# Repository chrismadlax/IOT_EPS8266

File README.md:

# IOT_EPS8266
IOT_EPS8266

for Maker's Attic 創客閣樓

_PCB: Eagle PCB project 

_CODE: uPy source code 

problem fix
	transistor T1 & T2 pin E/B must swap
	crystal can be remove
	resistance R19 can be short to GND

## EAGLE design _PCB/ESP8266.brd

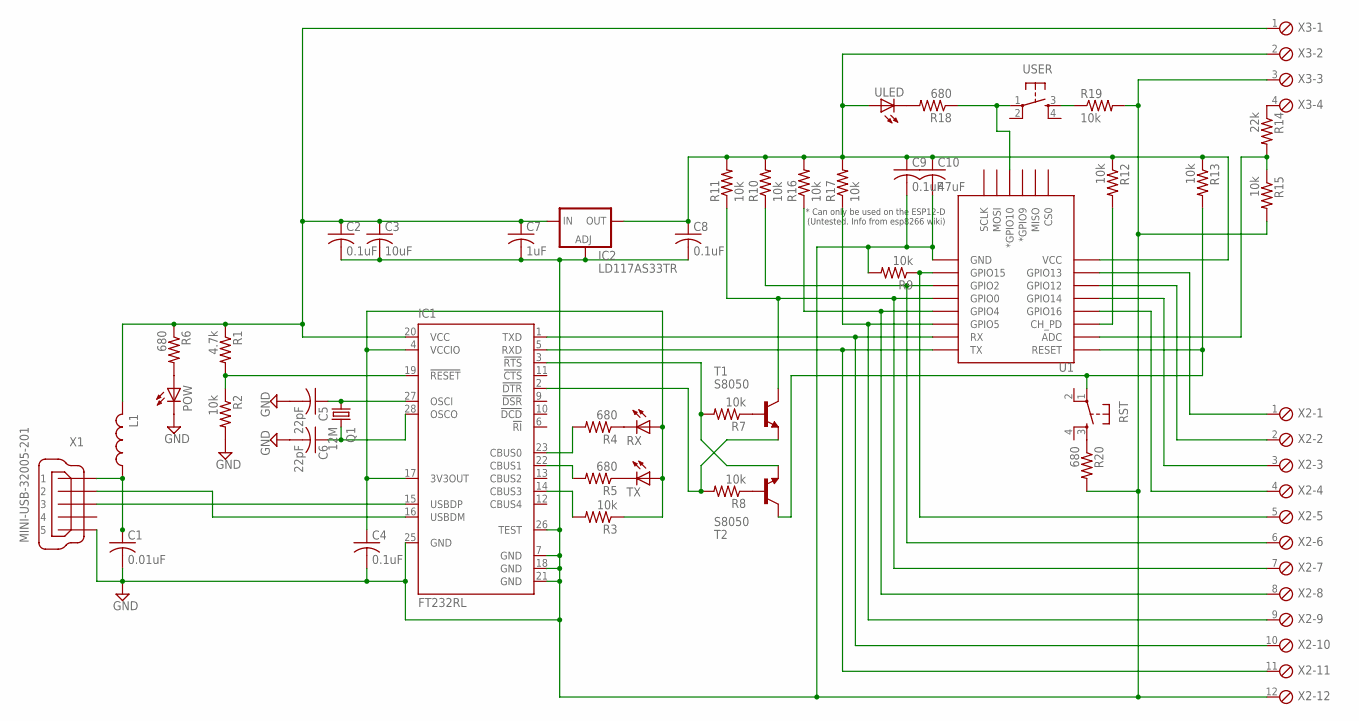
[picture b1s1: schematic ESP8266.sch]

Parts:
C1: 0.01uF; C0805
C2, C4, C8, C9: 0.1uF; C0805
C3: 10uF; C0805
C5, C6: 22pF; C0805
C7: 1uF; C0805
C10: 47uF; C0805
IC1: FT232RL; SSOP28
IC2: LD117AS33TR; SOT223
L1: L-USL2012C; L2012C
POW: LEDCHIP-LED0805; CHIP-LED0805
Q1: 12M; SM49
R1: 4.7k; R0805
R2, R3, R7, R8, R9, R10, R11, R12, R13, R15, R16, R17, R19: 10k; R0805
R4, R5, R6, R18, R20: 680; R0805
R14: 22k; R0805
RST: DTSM-6
RX: LEDCHIP-LED0805; CHIP-LED0805
T1, T2: S8050; SOT23-BEC
TX: LEDCHIP-LED0805; CHIP-LED0805
U1: ESP12ESMD; ESP12E-SMD
ULED: LEDCHIP-LED0805; CHIP-LED0805
USER: DTSM-6
X1: MINI-USB-32005-201; 32005-201
X2: MPT12; 12POL254
X3: MPT4; 4POL254

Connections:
GND: C1.2, C2.2, C3.2, C4.2, C5.2, C6.2, C7.2, C8.2, C9.2, C10.2, IC1.7 (GND), IC1.18 (GND), IC1.21 (GND), IC1.25 (GND), IC1.26 (TEST), IC2.1 (ADJ), POW.C, R2.2, R9.2, R15.2, R19.2, R20.2, U1.GND, X1.5, X2.12, X3.3
unnamed: POW.A, R6.2
unnamed: IC1.15 (USBDP), X1.3
unnamed: IC1.16 (USBDM), X1.2
unnamed: C5.1, IC1.27 (OSCI), Q1.1
unnamed: C6.1, IC1.28 (OSCO), Q1.2
unnamed: IC1.19 (!RESET), R1.2, R2.1
unnamed: IC1.14 (CBUS3), R3.2
unnamed: IC1.22 (CBUS1), R5.2
unnamed: IC1.23 (CBUS0), R4.2
unnamed: R4.1, RX.C
unnamed: R5.1, TX.C
unnamed: IC1.1 (TXD), U1.RXD0 (RX), X2.10
unnamed: IC1.5 (RXD), U1.TXD0 (TX), X2.11
unnamed: R7.1, T1.B
unnamed: R8.1, T2.B
unnamed: IC1.3 (!RTS), R7.2, T2.E
unnamed: IC1.2 (!DTR), R8.2, T1.E
unnamed: R10.1, U1.GPIO2, X2.6
unnamed: R9.1, U1.GPIO15, X2.5
unnamed: R16.1, U1.GPIO4, X2.8
unnamed: R12.2, U1.CH_PD
unnamed: R13.2, RST.1, T2.C, U1.RESET
unnamed: C4.1, IC1.4 (VCCIO), IC1.17 (3V3OUT), R3.1, RX.A, TX.A
unnamed: R14.2, R15.1, U1.ADC
unnamed: R17.1, U1.GPIO5, X2.9
unnamed: R11.1, T1.C, U1.GPIO0, X2.7
unnamed: R18.2, ULED.C
unnamed: R18.1, U1.GPIO10 (*GPIO10), USER.1
unnamed: R19.1, USER.3
unnamed: R14.1, X3.4
unnamed: R20.1, RST.3
unnamed: U1.GPIO13, X2.1
unnamed: U1.GPIO12, X2.2
unnamed: U1.GPIO14, X2.3
unnamed: U1.GPIO16, X2.4
V33E: C8.1, C9.1, C10.1, IC2.4 (OUT), R10.2, R11.2, R12.1, R13.1, R16.2, R17.2, U1.VCC, ULED.A, X3.2
VBUS: C1.1, L1.1, X1.1
VCC: C2.1, C3.1, C7.1, IC1.20 (VCC), IC2.3 (IN), L1.2, R1.1, R6.1, X3.1

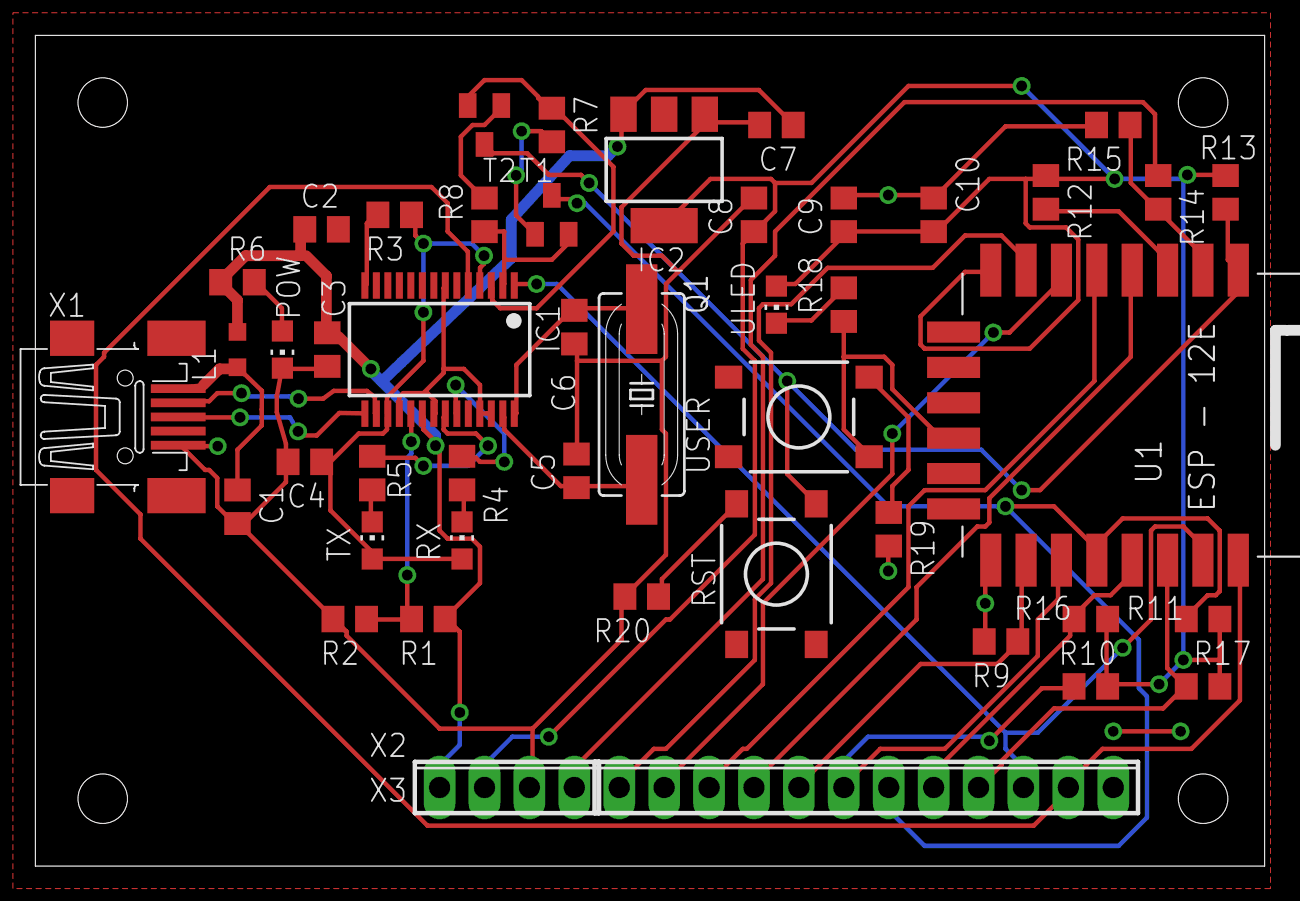
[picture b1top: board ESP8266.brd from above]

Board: 2 copper layers, 69.5 x 47.0 mm, 46 parts (0 on the bottom side), 39 nets.

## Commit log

2017-06-09 both PCB project & uPython CODE
2017-06-09 Clear file
2017-06-09 add Resource.txt
2017-06-10 edit mask CNC path
2017-06-13 update problem fix infomation in README.md and "test.py" for first test
2017-06-14 change main.py for board test, and add ds18b20.py for temp sensor test
2017-06-14 fix transistor pin E/B swap process
2017-06-14 Add work photo
2017-06-26 add main_web.py
2017-06-29 edit ds18b20.py runt is one time
2017-06-29 add web_dht11.py
2019-04-05 新增1.10版 firmware 與修正Pin語法
